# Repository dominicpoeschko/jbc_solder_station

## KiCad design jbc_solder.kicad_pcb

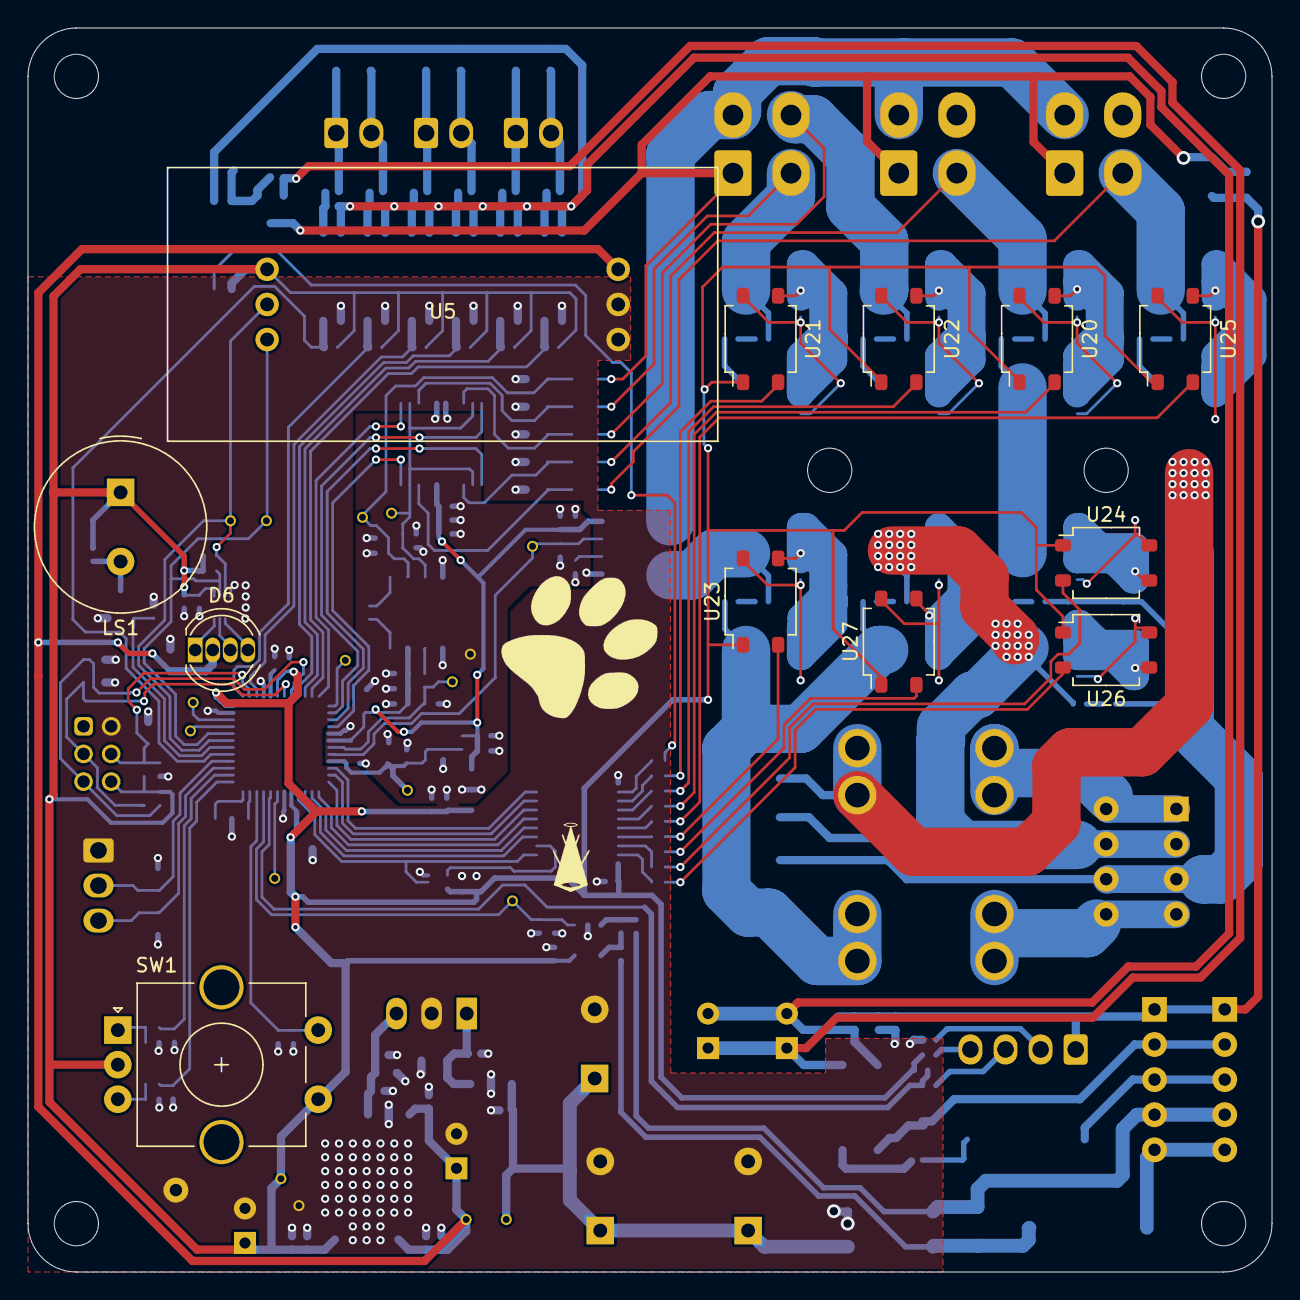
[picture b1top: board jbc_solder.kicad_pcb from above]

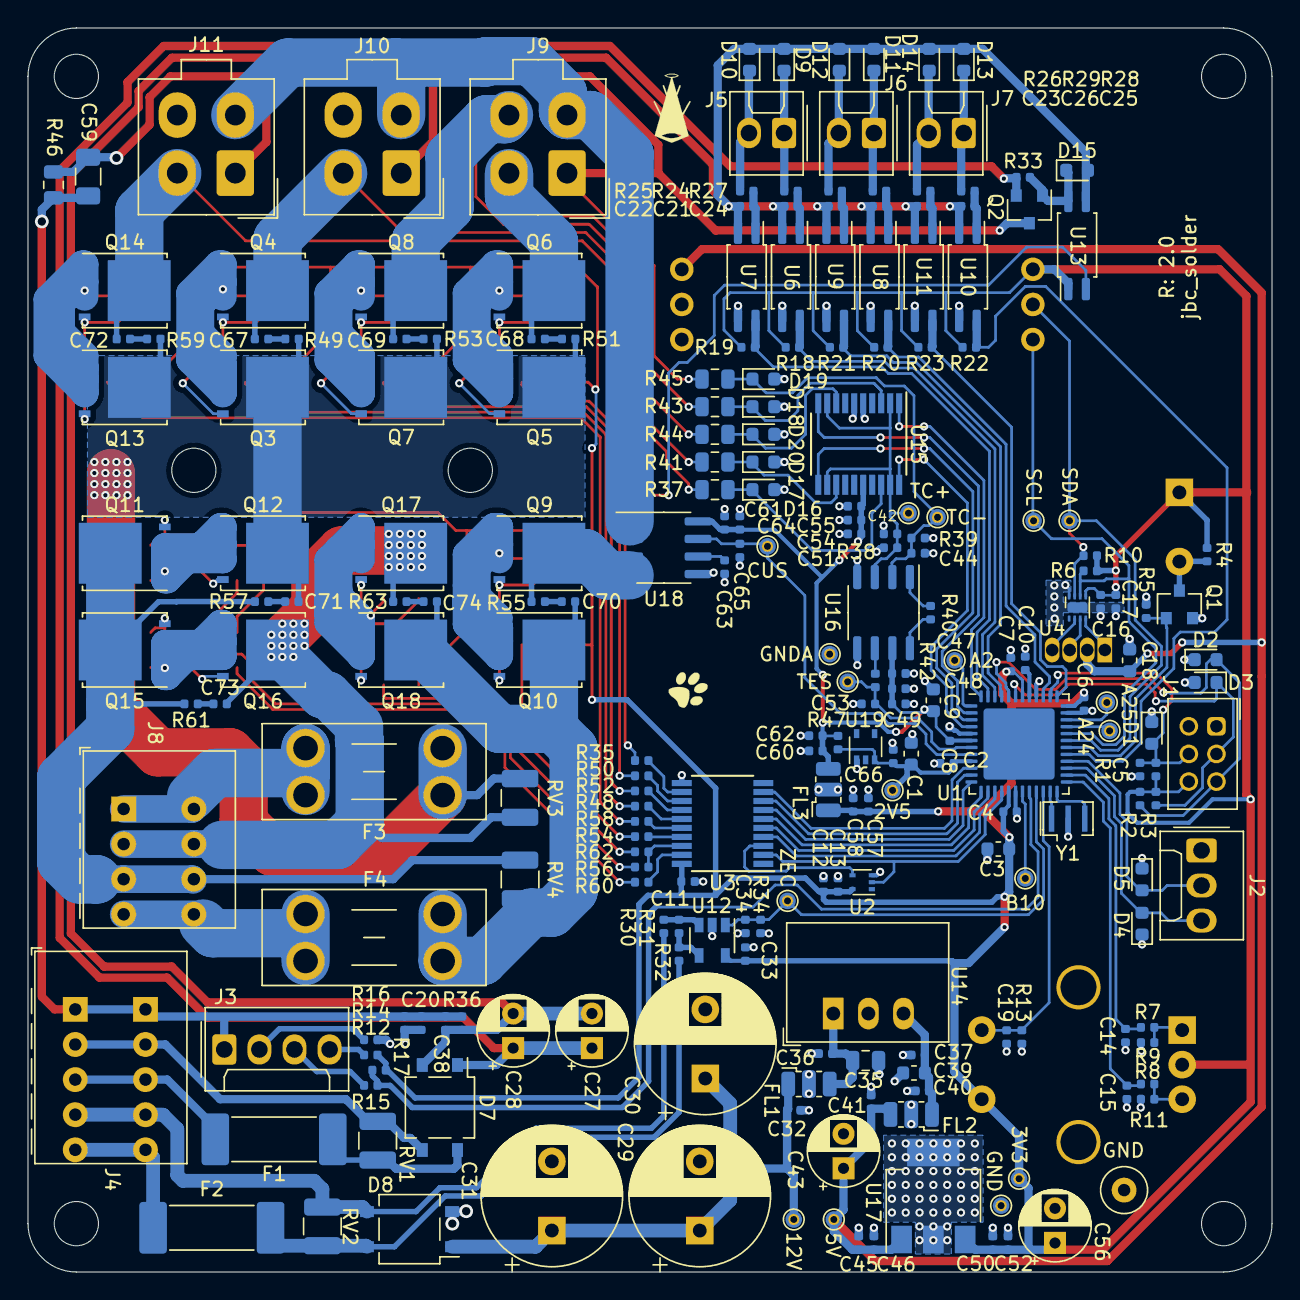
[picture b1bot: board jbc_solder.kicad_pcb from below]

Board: 2 copper layers, 90.0 x 90.0 mm, 251 parts (233 on the bottom side), 145 nets.

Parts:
C1, C3, C9, C18, C39: 10uF; C_0603_1608Metric
C2, C4, C6, C7, C8, C12, C13, C17, C20, C32, C33, C36, C37, C38, C40, C41, C46, C48, C50, C54, C58, C60, C61, C66, C67, C68, C69, C70, C71, C72, C73, C74: 100nF; C_0402_1005Metric
C5, C14, C15, C19, C21, C22, C23, C24, C25, C26, C47, C55, C63: 10nF; C_0402_1005Metric
C10, C16: 1uF; C_0402_1005Metric
C11, C45, C49, C51, C52, C57, C62, C64: 2.2uF; C_0402_1005Metric
C27, C28, C43, C56: 47uF; CP_Radial_D5.0mm_P2.50mm
C29, C30, C31: 470uF; CP_Radial_D10.0mm_P5.00mm
C34, C53, C65: 1nF; C_0402_1005Metric
C35: 4.7uF; C_0805_2012Metric
C42, C44: 15pF; C_0402_1005Metric
C59: 100nF; C_1206_3216Metric
D1, D2, D3, D4, D5, D9, D10, D11, D12, D13, D14, D15, D16, D17, D18, D19, D20: 3V3; D_0603_1608Metric
D6: LED_RABG; LED_D5.0mm-4_RGB
D7, D8: MBS8; TO-269AA
F1: 100mA; Fuse_Schurter_UMT250
F2: 1A; Fuse_Schurter_UMT250
F3, F4: 10A; Fuseholder_Blade_Mini_Keystone_3568
FL1, FL2, FL3: EMI_Filter_LCL; 3Pole_F1206
HOLE1, HOLE2, HOLE3, HOLE4: MountingHole_3.2mm_M3
HS_HOLE1, HS_HOLE2: MountingHole_3.2mm_M3
J1: SWD; DF11-6DP-2DSA
J2: UART; molex_022112032
J3: TRAFO_TEMP; molex_022112042
J4: TerminalBlock_KF141v-5-2.54_1x05_P2.54mm_Horizontal
J5: TIP1_SR; molex_022112022
J6: TIP2_SR; molex_022112022
J7: TIP3_SR; molex_022112022
J8: TerminalBlock_KF141v-4-2.54_1x04_P2.54mm_Horizontal
J9: TIP3; Molex_Mini-Fit_Jr_87427-0444_2x02_P4.20mm_Vertical
J10: TIP2; Molex_Mini-Fit_Jr_87427-0444_2x02_P4.20mm_Vertical
J11: TIP1; Molex_Mini-Fit_Jr_87427-0444_2x02_P4.20mm_Vertical
LS1: Speaker_Crystal; Buzzer_TDK_PS1240P02BT_D12.2mm_H6.5mm
Q1: PMV164ENEAR; SOT-23
Q2: DMN61D8LQ-13; SOT-23
Q3, Q4, Q5, Q6, Q7, Q8, Q9, Q10, Q11, Q12, Q13, Q14, Q15, Q16, Q17, Q18: BSC098N10NS5; TDSON-8-1
R1, R3, R5, R7, R8, R9, R11, R13, R18, R19, R20, R21, R22, R23, R31, R33, R40: 10k; R_0402_1005Metric
R2, R30, R32, R34: 100k; R_0402_1005Metric
R4: 1k; R_0402_1005Metric
R6, R10, R12: 4k7; R_0402_1005Metric
R14, R15, R16: 27R; R_0402_1005Metric
R17, R36, R38, R39: 1M; R_0402_1005Metric
R24, R25, R26, R27, R28, R29, R42, R47: 560R; R_0402_1005Metric
R35, R48, R49, R50, R51, R52, R53, R54, R55, R56, R57, R58, R59, R60, R61, R62, R63: 220R; R_0402_1005Metric
R37, R41, R43, R44, R45: 22k; R_0805_2012Metric
R46: 1M; R_0805_2012Metric
RV1, RV2, RV3, RV4: 30V; R_1210_3225Metric
SW1: Rotary_Encoder_Switch; RotaryEncoder_Alps_EC11E-Switch_Vertical_H20mm_CircularMoun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
TP1: A24; TestPoint_Pad_D1.2mm_0.5mmHole
TP2: A25; TestPoint_Pad_D1.2mm_0.5mmHole
TP3: A2; TestPoint_Pad_D1.2mm_0.5mmHole
TP4: B10; TestPoint_Pad_D1.2mm_0.5mmHole
TP5: SCL; TestPoint_Pad_D1.2mm_0.5mmHole
TP6: SDA; TestPoint_Pad_D1.2mm_0.5mmHole
TP7: 12V; TestPoint_Pad_D1.2mm_0.5mmHole
TP8: ZEC; TestPoint_Pad_D1.2mm_0.5mmHole
TP9: TC-; TestPoint_Pad_D1.2mm_0.5mmHole
TP10: TC+; TestPoint_Pad_D1.2mm_0.5mmHole
TP11: 5V; TestPoint_Pad_D1.2mm_0.5mmHole
TP12: GNDA; TestPoint_Pad_D1.2mm_0.5mmHole
TP13: 3V3; TestPoint_Pad_D1.2mm_0.5mmHole
TP14: GND; TestPoint_Loop_D2.60mm_Drill0.9mm_Beaded
TP15: TES; TestPoint_Pad_D1.2mm_0.5mmHole
TP16: GND; TestPoint_Pad_D1.2mm_0.5mmHole
TP17: CUS; TestPoint_Pad_D1.2mm_0.5mmHole
TP18: 2V5; TestPoint_Pad_D1.2mm_0.5mmHole
U1: ATSAMD21G17L; QFN-48-1EP_7x7mm_P0.5mm_EP5.15x5.15mm
U2: 74LVC1GU04DRL; SOT-553
U3: TLC59211; TSSOP-20_4.4x6.5mm_P0.65mm
U4: KTD2026; UTDFN-8-1EP_1.5x1.5mm_P0.4mm_EP0.8x1.45mm
U5: 7Seg_I2C_Display
U6, U7, U8, U9, U10, U11, U13: TCMT1100; SOP-4_4.4x2.6mm_P1.27mm
U12: TS881xLx; SOT-23-5
U14: R-78E5.0-0.5; Converter_DCDC_RECOM_R-78E-0.5_THT
U15: ADG734; TSSOP-20_4.4x6.5mm_P0.65mm
U16: LT1789; SO-8_3.9x4.9mm_P1.27mm
U17: LM3940IMP-3.3_SOT223; SOT-223-3_TabPin2
U18: ACS725xLCTR-20AB; SOIC-8_3.9x4.9mm_P1.27mm
U19: LM4040DCK-2.5; SOT-353_SC-70-5
U20, U21, U22, U23, U24, U25, U26, U27: VOM1271T; SOP-4_4.6x4.9_P2.54mm
Y1: 8MHz; Resonator_SMD_muRata_CSTxExxV-3Pin_3.0x1.1mm

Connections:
+2V5: C1.2, C2.1, C66.1, R47.1, TP18.1, U1.9, U19.3
+3.3VA: C8.1, C9.2, C47.1, C48.1, C49.2, C51.2, C54.1, C55.1, C60.1, C61.1, C62.2, C64.2, FL3.3, R47.2, U1.6, U15.16, U16.7, U18.8
+3V3: C3.2, C4.1, C6.1, C7.1, C11.2, C12.1, C13.1, C16.2, C17.1, C33.1, C50.1, C52.2, C56.1, C57.2, C58.1, FL3.1, J1.6, LS1.1, R1.1, R2.1, R3.1, R4.2, R6.2, R10.2, R12.2, R14.2, R18.2, R19.2, R20.2, R21.2, R22.2, R23.2, SW1.C, SW1.S1, TP13.1, U1.17, U1.36, U1.42, U2.5, U3.20, U4.5, U5.1, U12.5, U13.1, U17.3, U20.1, U21.1, U22.1, U23.1, U24.1, U25.1, U26.1, U27.1
+5V: C18.2, C41.1, C43.1, C45.2, C46.1, D6.2, FL2.3, TP11.1, U5.6, U17.1
+5VL: C27.1, C28.1, D7.1, Q2.2, R33.1
+5VP: C37.1, C39.2, C40.1, FL2.1, U14.3
+12V: C29.1, C30.1, C31.1, C32.1, D8.1, FL1.1, TP7.1
/24_48_SELECT: U1.16, U2.2, U3.2
/24_SW_I: U2.4, U3.3
/A2: TP3.1, U1.1
/B10: TP4.1, U1.19
/CURRENT_SENSE: C65.1, TP17.1, U1.8, U18.7
/DEBUG_RX: D5.2, J2.2, U1.28
/DEBUG_TX: D4.2, J2.3, U1.27
/LED_B_I: D6.3, U4.3
/LED_G_I: D6.4, U4.2
/LED_R_I: D6.1, U4.4
/OSC_IN: U1.23, Y1.1
/OSC_OUT: U1.24, Y1.3
/PA24: TP1.1, U1.33
/PA25: TP2.1, U1.34
/PIEZO: Q1.1, R5.1, U1.30
/PIEZO_GND: LS1.2, Q1.3, R4.1
/ROTARY_A: C14.1, R7.2, U1.26
/ROTARY_A_RAW: R7.1, R9.1, SW1.A
/ROTARY_B: C15.1, R8.2, U1.25
/ROTARY_B_RAW: R8.1, R11.1, SW1.B
/ROTARY_SW: C19.1, R13.1, SW1.S2, U1.22
/SCL: R6.1, TP5.1, U1.32, U4.6, U5.3
/SDA: R10.1, TP6.1, U1.31, U4.7, U5.2
/SLEEP_SW_UC: U1.10, U3.9
/SWCLK: D3.1, J1.3, R3.2, U1.43
/SWDIO: D2.2, J1.5, R2.2, U1.44
/TEMP_SENSE: C53.1, R42.1, TP15.1, U1.7
/TIP1_REMOVE: R19.1, U1.47, U7.4
/TIP1_SLEEP: R18.1, U1.46, U6.4
/TIP1_SW_UC: U1.14, U3.5
/TIP1_TC_SW: U1.4, U15.20
/TIP2_REMOVE: R21.1, U1.45, U9.4
/TIP2_SLEEP: R20.1, U1.39, U8.4
/TIP2_SW_UC: U1.13, U3.6
/TIP2_TC_SW: U1.3, U15.11
/TIP3_REMOVE: R23.1, U1.37, U11.4
/TIP3_SLEEP: R22.1, U1.29, U10.4
/TIP3_SW1_UC: U1.11, U3.8
/TIP3_SW2_UC: U1.12, U3.7
/TIP3_TC_SW1: U1.48, U15.1
/TIP3_TC_SW2: U1.2, U15.10
/TIP_COM_SW_UC: U1.15, U3.4
/TRAFO_TEMP: R12.1, R15.2, U1.20
/TRAFO_TEMP_GND: J3.2, R16.1
/TRAFO_TEMP_SIGNAL: J3.3, R15.1
/TRAFO_TEMP_VCC: J3.4, R14.1
/VDD_CORE: C10.2, U1.41
/ZERO_CROSS: C34.1, R34.1, TP8.1, U1.21, U12.1
/tip_control/24V_SW: R56.1, R62.1, U3.18
/tip_control/24V_SW_1/SWITCH_G: Q17.4, Q18.4, U27.4
/tip_control/24V_SW_1/SWITCH_S: Q17.1, Q17.2, Q17.3, Q18.1, Q18.2, Q18.3, U27.3
/tip_control/24V_SW_1/SWITCH_SNUBBER: C74.1, R63.1
/tip_control/24V_SW_1/SWITCH_SW_LED_I1: R62.2, U27.2
/tip_control/24V_SW_2/SWITCH_G: Q11.4, Q12.4, U24.4
/tip_control/24V_SW_2/SWITCH_S: Q11.1, Q11.2, Q11.3, Q12.1, Q12.2, Q12.3, U24.3
/tip_control/24V_SW_2/SWITCH_SNUBBER: C71.1, R57.1
/tip_control/24V_SW_2/SWITCH_SW_LED_I1: R56.2, U24.2
/tip_control/48V_SW: R60.1, U3.19
/tip_control/48V_SW/SWITCH_G: Q15.4, Q16.4, U26.4
/tip_control/48V_SW/SWITCH_S: Q15.1, Q15.2, Q15.3, Q16.1, Q16.2, Q16.3, U26.3
/tip_control/48V_SW/SWITCH_SNUBBER: C73.1, R61.1
/tip_control/48V_SW/SWITCH_SW_LED_I1: R60.2, U26.2
/tip_control/+12_F: C35.2, C36.1, FL1.3, U14.1
/tip_control/AC1_HEATER_24V_48V: C70.2, C74.2, F4.1, Q10.5, Q18.5, RV4.1
/tip_control/AC1_I: R31.1, R32.1, U12.4
/tip_control/AC2_HEATER_24V_48V: C71.2, F3.1, Q3.5, Q5.5, Q7.5, Q12.5, Q13.5, R49.2, R51.2, R53.2, R59.2, RV3.2
/tip_control/AC2_I: R30.2, R31.2, U12.3
/tip_control/AC_4V_1: F1.2, J4.3
/tip_control/AC_4V_1_FUSED: D7.4, F1.1, RV1.1
/tip_control/AC_4V_2: D7.3, J4.2, RV1.2
/tip_control/AC_12V_1: F2.2, J4.5
/tip_control/AC_12V_1_FUSED: D8.4, F2.1, R32.2, RV2.2
/tip_control/AC_12V_2: D8.3, J4.4, R30.1, RV2.1
/tip_control/AC_24V_GREY: C73.2, J8.2, Q16.5, Q17.5, R63.2, RV3.1
/tip_control/AC_24V_ORANGE: F3.2, J8.1
/tip_control/AC_24V_RED: F4.2, J8.4
/tip_control/AC_24_BLACK: J8.3, Q11.5, Q15.5, R57.2, R61.2, RV4.2
/tip_control/COMMON_SW/SWITCH_G: Q9.4, Q10.4, U23.4
/tip_control/COMMON_SW/SWITCH_S: Q9.1, Q9.2, Q9.3, Q10.1, Q10.2, Q10.3, U23.3
/tip_control/COMMON_SW/SWITCH_SNUBBER: C70.1, R55.1
/tip_control/COMMON_SW/SWITCH_SW_LED_I1: R54.2, U23.2
/tip_control/CURRENT_FILTER: C63.1, U18.6
/tip_control/IP-: Q9.5, R55.2, U18.3, U18.4
/tip_control/RG1: R40.2, U16.1
/tip_control/RG2: R40.1, U16.8
/tip_control/SLEEP_SW: R35.2, U3.12
/tip_control/SLEEP_SW_I1: R35.1, U13.2
/tip_control/SLEEP_SW_I2: D15.1, Q2.1, R33.2, U13.4
/tip_control/T1_REMOVE: D10.1, J5.2, R25.1
/tip_control/T1_R_I: C22.2, R25.2, U7.1
/tip_control/T1_SLEEP: D9.1, J5.1, R24.1
/tip_control/T1_S_I: C21.2, R24.2, U6.1
/tip_control/T1_TS_I: D16.1, R37.2, U15.18
/tip_control/T2_REMOVE: D12.1, J6.2, R27.1
/tip_control/T2_R_I: C24.2, R27.2, U9.1
/tip_control/T2_SLEEP: D11.1, J6.1, R26.1
/tip_control/T2_S_I: C23.2, R26.2, U8.1
/tip_control/T2_TS_I: D17.1, R41.2, U15.13
/tip_control/T3_REMOVE: D14.1, J7.2, R29.1
/tip_control/T3_R_I: C26.2, R29.2, U11.1
/tip_control/T3_SLEEP: D13.1, J7.1, R28.1
/tip_control/T3_S_I: C25.2, R28.2, U10.1
/tip_control/T3_TS1_I: D18.1, R43.2, U15.3
/tip_control/T3_TS2_I: D20.1, R44.2, U15.8
/tip_control/TC+: C42.1, R38.2, TP10.1, U15.2, U15.9, U15.12, U15.19, U16.3
/tip_control/TC-: C44.1, D19.1, R39.1, R45.1, TP9.1, U16.2
/tip_control/TEMP_S_I: R42.2, U16.6
/tip_control/TIP1_SW: R58.1, U3.16
/tip_control/TIP1_SW/SWITCH_G: Q13.4, Q14.4, U25.4
/tip_control/TIP1_SW/SWITCH_S: Q13.1, Q13.2, Q13.3, Q14.1, Q14.2, Q14.3, U25.3
/tip_control/TIP1_SW/SWITCH_SNUBBER: C72.1, R59.1
/tip_control/TIP1_SW/SWITCH_SW_LED_I1: R58.2, U25.2
/tip_control/TIP1_TC: C72.2, J11.2, Q14.5, R37.1
/tip_control/TIP2_SW: R48.1, U3.15
/tip_control/TIP2_SW/SWITCH_G: Q3.4, Q4.4, U20.4
/tip_control/TIP2_SW/SWITCH_S: Q3.1, Q3.2, Q3.3, Q4.1, Q4.2, Q4.3, U20.3
/tip_control/TIP2_SW/SWITCH_SNUBBER: C67.1, R49.1
/tip_control/TIP2_SW/SWITCH_SW_LED_I1: R48.2, U20.2
/tip_control/TIP2_TC: C67.2, J10.2, Q4.5, R41.1
/tip_control/TIP3_SW1: R50.1, U3.13
/tip_control/TIP3_SW1/SWITCH_G: Q5.4, Q6.4, U21.4
/tip_control/TIP3_SW1/SWITCH_S: Q5.1, Q5.2, Q5.3, Q6.1, Q6.2, Q6.3, U21.3
/tip_control/TIP3_SW1/SWITCH_SNUBBER: C68.1, R51.1
/tip_control/TIP3_SW1/SWITCH_SW_LED_I1: R50.2, U21.2
/tip_control/TIP3_SW2: R52.1, U3.14
/tip_control/TIP3_SW2/SWITCH_G: Q7.4, Q8.4, U22.4
/tip_control/TIP3_SW2/SWITCH_S: Q7.1, Q7.2, Q7.3, Q8.1, Q8.2, Q8.3, U22.3
/tip_control/TIP3_SW2/SWITCH_SNUBBER: C69.1, R53.1
/tip_control/TIP3_SW2/SWITCH_SW_LED_I1: R52.2, U22.2
/tip_control/TIP3_TC1: C68.2, J9.2, Q6.5, R43.1
/tip_control/TIP3_TC2: C69.2, J9.4, Q8.5, R44.1
/tip_control/TIP_COM: J9.3, J10.3, J11.3, U18.1, U18.2
/tip_control/TIP_COM_SW: R54.1, U3.17
/tip_control/TIP_SHELL: C59.2, J9.1, J10.1, J11.1, Q2.3, R45.2, R46.2
/~RESET: C5.1, D1.2, J1.4, R1.2, U1.38
Earth: C20.1, C38.1, C59.1, J3.1, J4.1, R17.1, R36.1, R46.1
GND: C1.1, C2.2, C3.1, C4.2, C5.2, C6.2, C7.2, C8.2, C9.1, C10.1, C11.1, C12.2, C13.2, C14.2, C15.2, C16.1, C17.2, C18.1, C19.2, C20.2, C29.2, C30.2, C31.2, C32.2, C33.2, C34.2, C35.1, C36.2, C37.2, C39.1, C40.2, C41.2, C42.2, C43.2, C44.2, C45.1, C46.2, C47.2, C48.2, C49.1, C50.2, C51.1, C52.1, C53.2, C54.2, C55.2, C56.2, C57.1, C58.2, C60.2, C61.2, C62.1, C63.2, C64.1, C65.2, C66.2, D1.1, D2.1, D3.2, D4.1, D5.1, D8.2, D16.2, D17.2, D18.2, D19.2, D20.2, FL1.2, FL2.2, FL3.2, J1.2, J2.1, Q1.2, R5.2, R9.2, R11.2, R13.2, R16.2, R17.2, R34.2, R38.1, R39.2, TP12.1, TP14.1, TP16.1, U1.5, U1.18, U1.35, U1.40, U2.3, U3.11, U4.8, U4.9, U5.4, U5.5, U6.3, U7.3, U8.3, U9.3, U10.3, U11.3, U12.2, U14.2, U15.5, U15.6, U16.4, U16.5, U17.2, U18.5, U19.1, Y1.2
GND_ISO: C21.1, C22.1, C23.1, C24.1, C25.1, C26.1, C27.2, C28.2, C38.2, D7.2, D9.2, D10.2, D11.2, D12.2, D13.2, D14.2, D15.2, R36.2, U6.2, U7.2, U8.2, U9.2, U10.2, U11.2, U13.3

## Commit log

2024-02-16 copy of an old project
